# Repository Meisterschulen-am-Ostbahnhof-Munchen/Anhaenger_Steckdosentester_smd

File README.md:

# Anhaenger_Steckdosentester SMD

https://github.com/Meisterschulen-am-Ostbahnhof-Munchen/Anhaenger_Steckdosentester_smd/blob/master/README.md

## 3D Modelle für Autodesk Inventor und Fusion 360:

https://github.com/Meisterschulen-am-Ostbahnhof-Munchen/Anhaenger_Steckdosentester_smd/tree/master/3D

## Stücklisten

https://github.com/Meisterschulen-am-Ostbahnhof-Munchen/Anhaenger_Steckdosentester_smd/tree/master/BOM

## Platinen

### Platine_1

### Platine_2

## Montage

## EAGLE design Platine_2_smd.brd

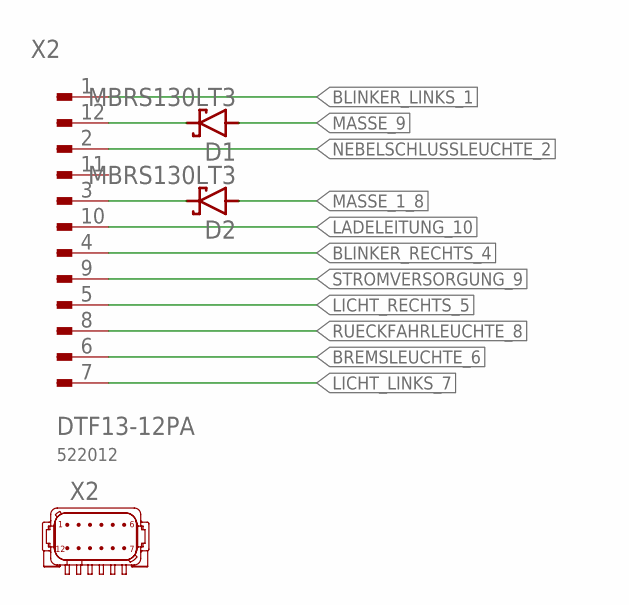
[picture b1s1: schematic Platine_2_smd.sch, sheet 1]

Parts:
D1, D2: MBRS130LT3; SMB
X2: DTF13-12PA

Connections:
BLINKER_LINKS_1: X2.1; also elsewhere on the board
BLINKER_RECHTS_4: X2.4; also elsewhere on the board
BREMSLEUCHTE_6: X2.6; also elsewhere on the board
LADELEITUNG_10: X2.10; also elsewhere on the board
LICHT_LINKS_7: X2.7; also elsewhere on the board
LICHT_RECHTS_5: X2.5; also elsewhere on the board
MASSE_1_8: D2.A; also elsewhere on the board
MASSE_9: D1.A; also elsewhere on the board
unnamed: D1.C, X2.12
unnamed: D2.C, X2.3
NEBELSCHLUSSLEUCHTE_2: X2.2; also elsewhere on the board
RUECKFAHRLEUCHTE_8: X2.8; also elsewhere on the board
STROMVERSORGUNG_9: X2.9; also elsewhere on the board

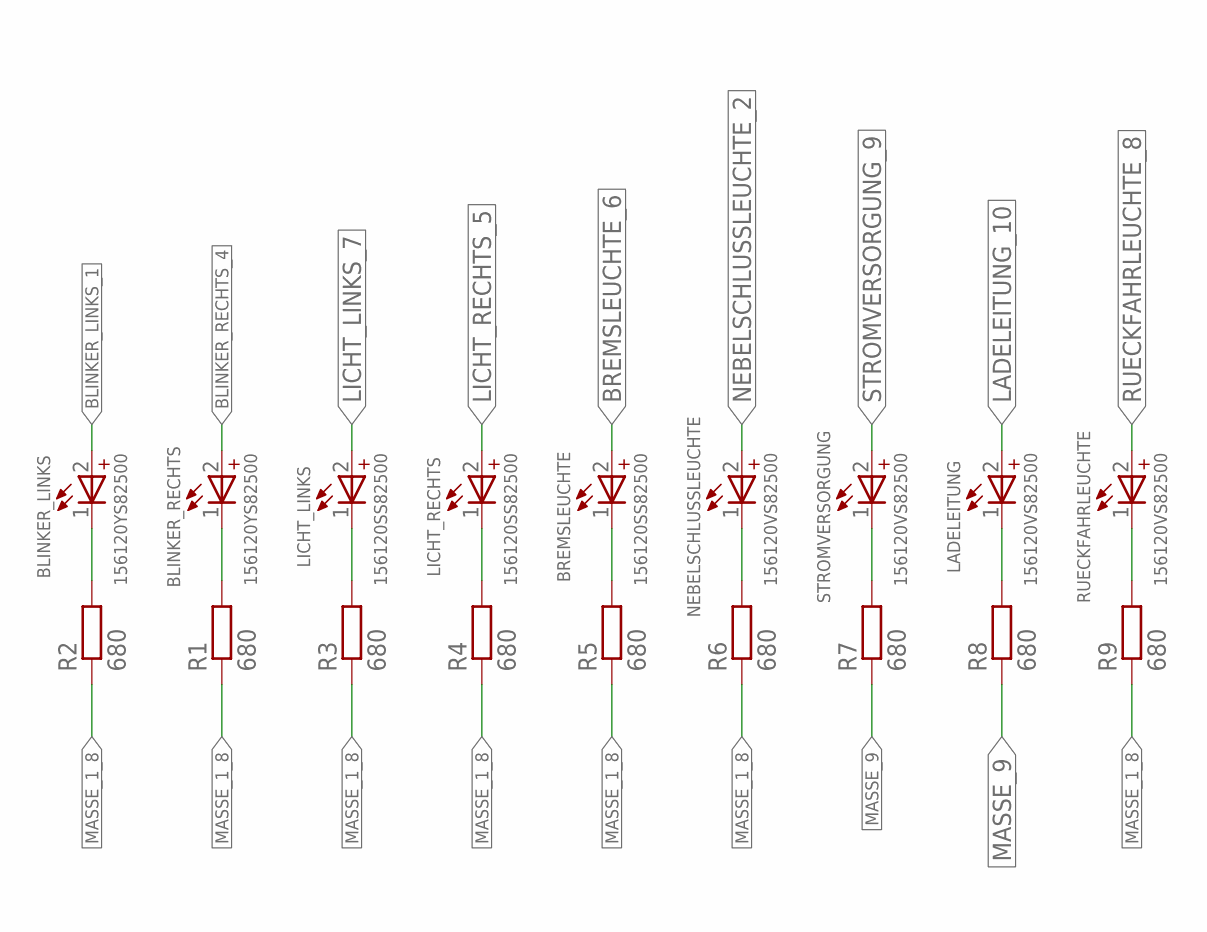
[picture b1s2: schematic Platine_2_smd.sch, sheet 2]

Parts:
BLINKER_LINKS: 156120YS82500; WL-SMRW_1206_DOME_REV
BLINKER_RECHTS: 156120YS82500; WL-SMRW_1206_DOME_REV
BREMSLEUCHTE: 156120SS82500; WL-SMRW_1206_DOME_REV
LADELEITUNG: 156120VS82500; WL-SMRW_1206_DOME_REV
LICHT_LINKS: 156120SS82500; WL-SMRW_1206_DOME_REV
LICHT_RECHTS: 156120SS82500; WL-SMRW_1206_DOME_REV
NEBELSCHLUSSLEUCHTE: 156120VS82500; WL-SMRW_1206_DOME_REV
R1, R2, R3, R4, R5, R6, R7, R8, R9: 680; R1206
RUECKFAHRLEUCHTE: 156120VS82500; WL-SMRW_1206_DOME_REV
STROMVERSORGUNG: 156120VS82500; WL-SMRW_1206_DOME_REV

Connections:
BLINKER_LINKS_1: BLINKER_LINKS.2 (+); also elsewhere on the board
BLINKER_RECHTS_4: BLINKER_RECHTS.2 (+); also elsewhere on the board
BREMSLEUCHTE_6: BREMSLEUCHTE.2 (+); also elsewhere on the board
LADELEITUNG_10: LADELEITUNG.2 (+); also elsewhere on the board
LICHT_LINKS_7: LICHT_LINKS.2 (+); also elsewhere on the board
LICHT_RECHTS_5: LICHT_RECHTS.2 (+); also elsewhere on the board
MASSE_1_8: R1.1, R2.1, R3.1, R4.1, R5.1, R6.1, R9.1; also elsewhere on the board
MASSE_9: R7.1, R8.1; also elsewhere on the board
unnamed: LICHT_LINKS.1 (-), R3.2
unnamed: LICHT_RECHTS.1 (-), R4.2
unnamed: BLINKER_LINKS.1 (-), R2.2
unnamed: BREMSLEUCHTE.1 (-), R5.2
unnamed: BLINKER_RECHTS.1 (-), R1.2
unnamed: NEBELSCHLUSSLEUCHTE.1 (-), R6.2
unnamed: R7.2, STROMVERSORGUNG.1 (-)
unnamed: LADELEITUNG.1 (-), R8.2
unnamed: R9.2, RUECKFAHRLEUCHTE.1 (-)
NEBELSCHLUSSLEUCHTE_2: NEBELSCHLUSSLEUCHTE.2 (+); also elsewhere on the board
RUECKFAHRLEUCHTE_8: RUECKFAHRLEUCHTE.2 (+); also elsewhere on the board
STROMVERSORGUNG_9: STROMVERSORGUNG.2 (+); also elsewhere on the board

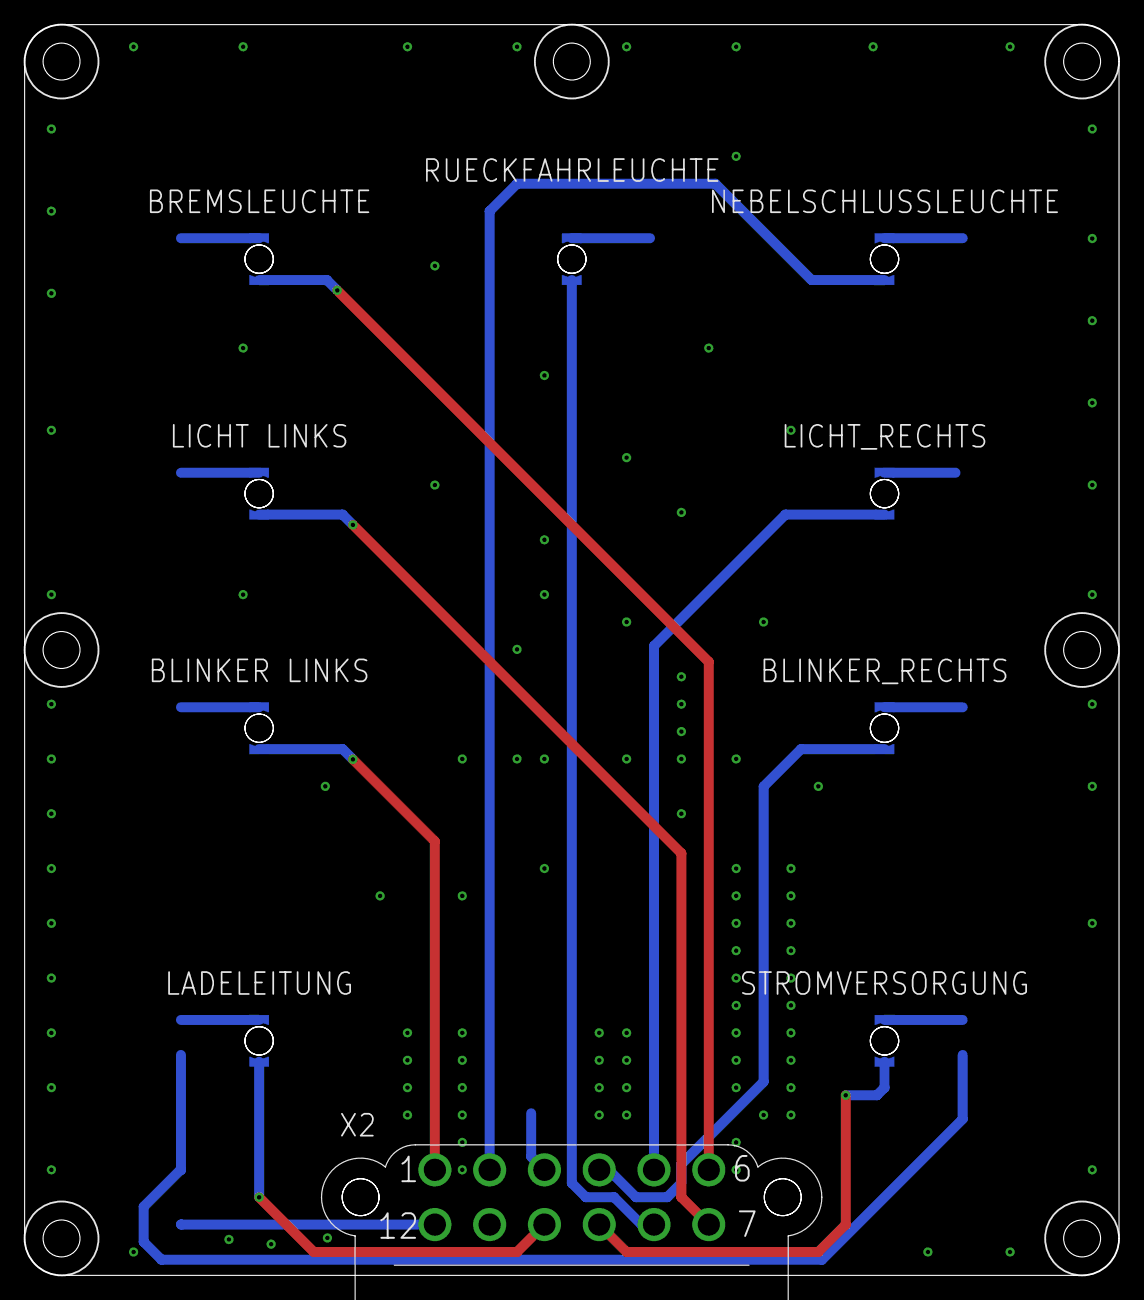
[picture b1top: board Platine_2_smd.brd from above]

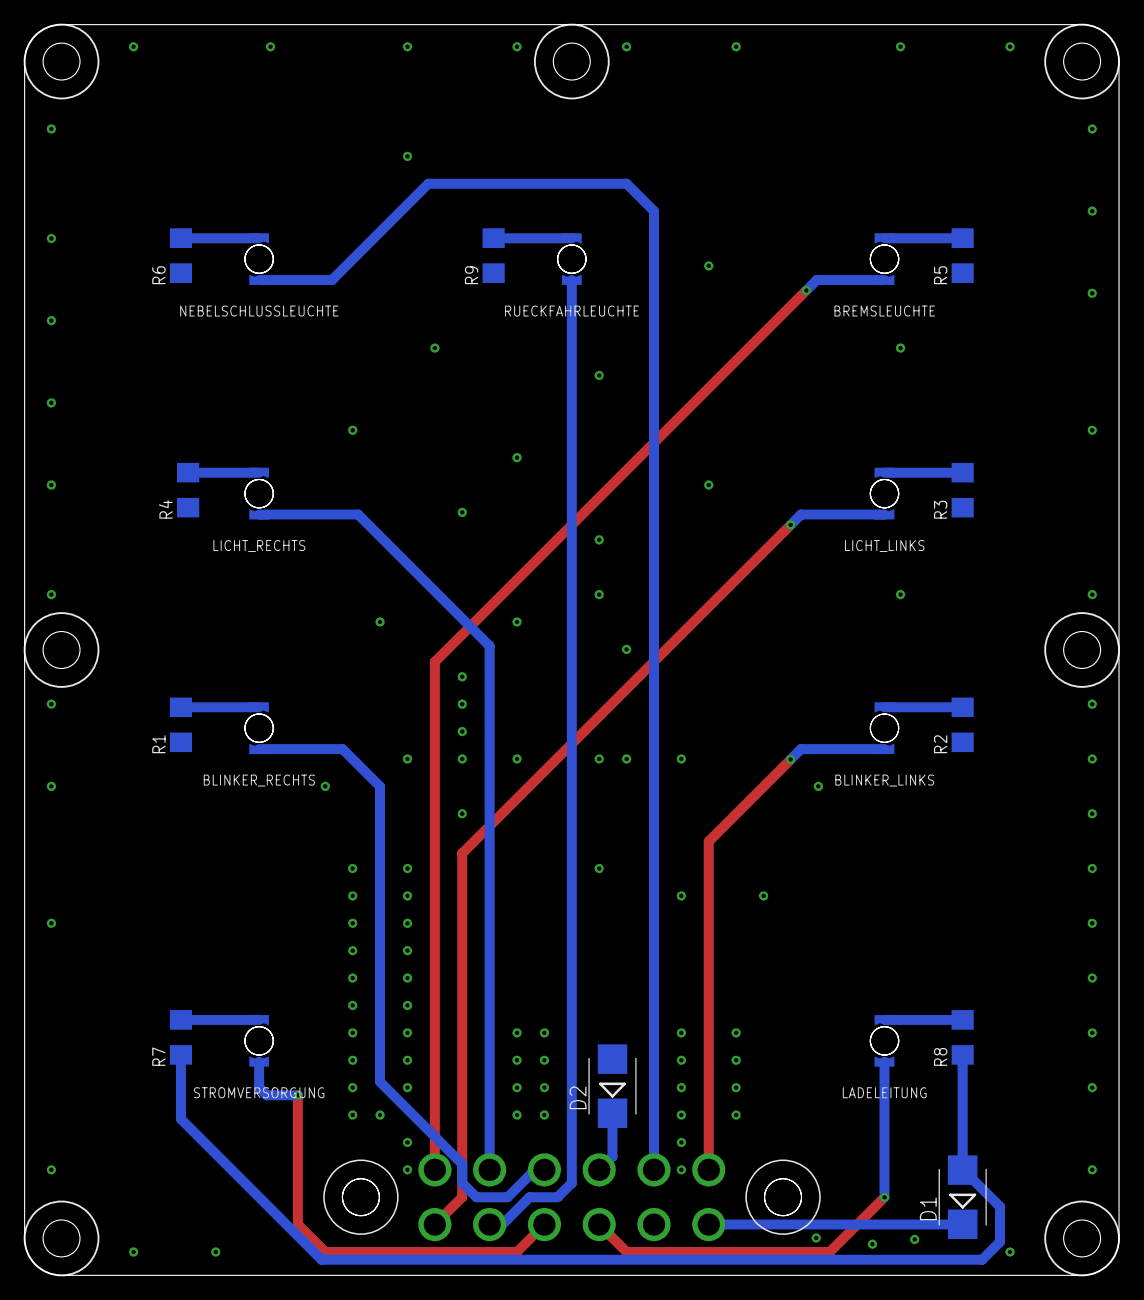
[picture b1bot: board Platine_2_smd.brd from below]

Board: 2 copper layers, 88.9 x 101.6 mm, 21 parts (20 on the bottom side), 22 nets.

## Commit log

2021-11-16 Done !
2021-11-17 Diode added !
2021-11-17 gitflow-feature-stash: Connector
2021-11-17 urn="urn:adsk.eagle:footprint:32238054/1
2021-11-17 3D Stecker !
2021-11-23 ISO1724_DOSE_TEST
2021-11-23 gitignore !
2021-11-26 both sided !
2021-11-30 git@github.com:Meisterschulen-am-Ostbahnhof-Munchen/elektro.git
2021-11-30 13P Stecker/Dose.
2021-11-30 Added submodule elektro-examples
2021-11-30 Updated submodule elektro-examples
2021-11-30 DXF.
2021-12-02 test it ...
2021-12-02 some Samples !
2022-11-18 Stücklise !
2022-11-18 Updated Libraries !
2022-11-18 Farben der LEDS
2022-11-18 Stückliste
2022-11-18 blinker gelb !
2022-11-18 PDFs
2022-11-21 DEUTSCH
2023-02-28 RM THT !
2023-03-01 fusion
2023-03-01 BOM and 3D !
2023-10-16 BOM and F360

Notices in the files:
parts and their libraries:
Wurth_LEDs_WL-SMRW: Copyright: Würth Elektronik
